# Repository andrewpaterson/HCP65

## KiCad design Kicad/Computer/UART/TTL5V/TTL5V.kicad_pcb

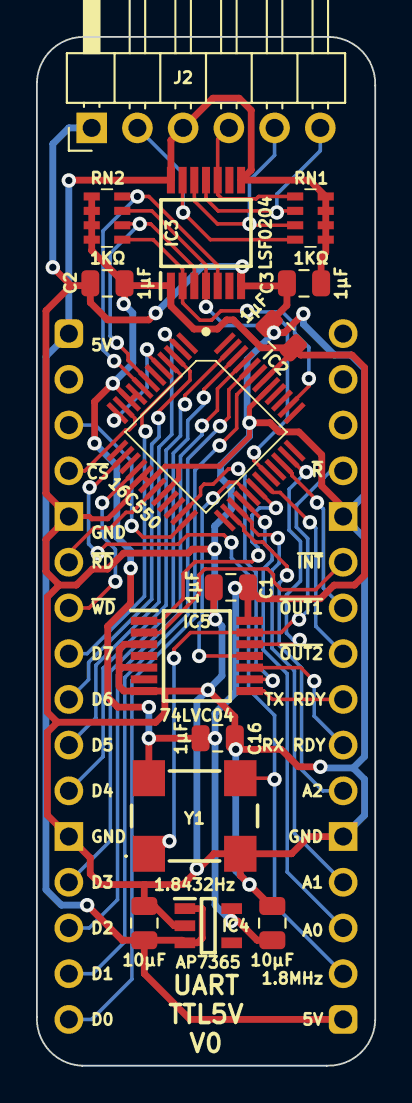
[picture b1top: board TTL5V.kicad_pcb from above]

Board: 2 copper layers, 18.8 x 57.2 mm, 16 parts (0 on the bottom side), 38 nets.

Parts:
C1, C2, C3, C15, C16: 1μF; C_0805
C17, C18: 10µF; C_0805
IC2: TL16C550DPTR; QFP50P900X900X160-48N
IC3: LSF0204PW-Q100J; SOP65P640X110-14N
IC4: AP7365-33WG-7; SOT95P285X130-5N
IC5: 74LVC04APW,118; SOP65P640X110-14N
J1: Board 2x16 W15.24mm; DIP-32_Board_W15.24mm_Nak
J2: Conn_01x06_Pin; PinHeader_1x06_P2.54mm_Horizontal
RN1, RN2: CAY16-102J4LF; CAY16-J4
Y1: LFSPXO020733

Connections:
1.8432MHz: IC2.14 (XIN), J1.18, Y1.3 (OUTPUT)
5V: C3.1, C17.1, IC3.8 (EN), IC3.14 (REFB), IC4.1 (6VIn), IC4.3 (EN), J1.1, J1.17, J2.3, RN1.5 (R4), RN1.6 (R3), RN1.7 (R2), RN1.8 (R1)
/3.3V: C1.1, C2.1, C15.1, C16.1, C18.1, IC2.9 (CS0), IC2.10 (CS1), IC2.42 (5V), IC3.1 (REFA), IC4.5 (3.3VOut), IC5.14 (3V), RN2.5 (R4), RN2.6 (R3), RN2.7 (R2), RN2.8 (R1), Y1.4 (3V)
/INT: IC2.30 (INTRPT), IC5.1 (1A)
/Reset: IC2.35 (MR), IC5.12 (6Y)
/SIN_{3V}: IC2.7 (SIN), IC3.3 (A1), RN2.2 (R2)
/SIN_{5V}: IC3.12 (B1), J2.5, RN1.3 (R3)
/SOUT_{3V}: IC2.8 (SOUT), IC3.5 (A3), RN2.4 (R4)
/SOUT_{5V}: IC3.10 (B3), J2.4, RN1.1 (R1)
/~CTS_{3V}: IC2.38 (~CTS), IC3.2 (A0), RN2.1 (R1)
/~CTS_{5V}: IC3.13 (B0), J2.2, RN1.4 (R4)
/~RTS_{3V}: IC2.32 (~RTS), IC3.4 (A2), RN2.3 (R3)
/~RTS_{5V}: IC3.11 (B2), J2.6, RN1.2 (R2)
/~RXRDY: IC2.29 (~RXRDY), IC5.11 (5A)
/~TXRDY: IC2.23 (~TXRDY), IC5.9 (4A)
A0: IC2.28 (A0), J1.19
A1: IC2.27 (A1), J1.20
A2: IC2.26 (A2), J1.22
D0: IC2.43 (D0), J1.16
D1: IC2.44 (D1), J1.15
D2: IC2.45 (D2), J1.14
D3: IC2.46 (D3), J1.13
D4: IC2.47 (D4), J1.11
D5: IC2.2 (D5), J1.10
D6: IC2.3 (D6), J1.9
D7: IC2.4 (D7), J1.8
GND: C1.2, C2.2, C3.2, C15.2, C16.2, C17.2, C18.2, IC2.17 (WR2), IC2.18 (GND), IC2.20 (RD2), IC2.41 (~RI), IC3.7 (GND), IC4.2 (GND), IC5.3 (2A), IC5.5 (3A), IC5.7 (GND), J1.5, J1.12, J1.21, J1.28, J2.1, Y1.2 (GND)
unnamed: IC2.5 (RCLK), IC2.12 (~BAUDOUT)
RX Ready: IC5.10 (5Y), J1.23
TX Ready: IC5.8 (4Y), J1.24
~ADS: IC2.24 (~ADS), J1.3
~CS: IC2.11 (~CS2), J1.4
~INT: IC5.2 (1Y), J1.27
~OUT1: IC2.34 (~OUT1), J1.26
~OUT2: IC2.31 (~OUT2), J1.25
~RD: IC2.19 (~RD1), J1.6
~Reset: IC5.13 (6A), J1.29, Y1.1 (EN)
~WD: IC2.16 (~WR1), J1.7

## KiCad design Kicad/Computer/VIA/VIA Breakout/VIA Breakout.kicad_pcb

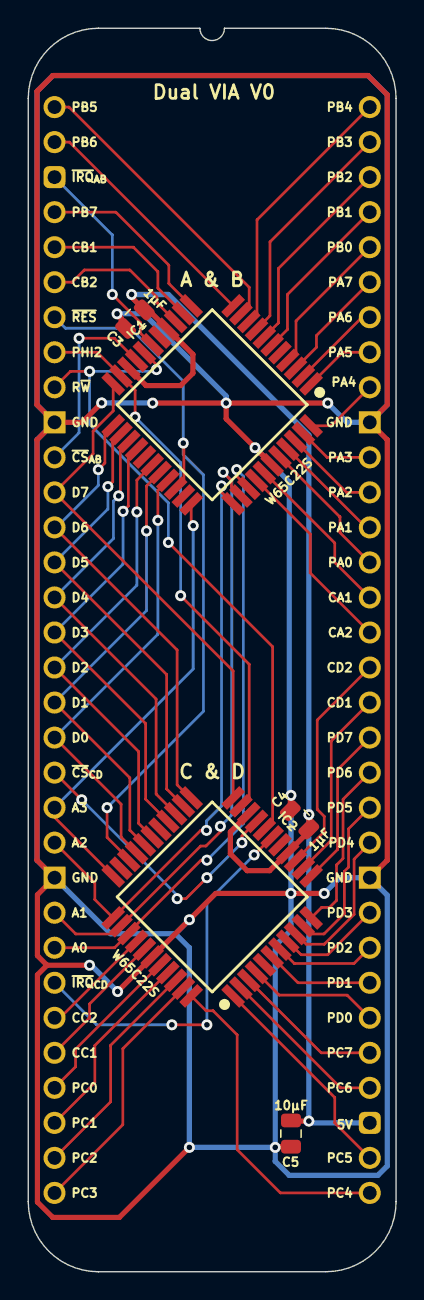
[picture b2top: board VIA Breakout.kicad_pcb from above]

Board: 2 copper layers, 26.7 x 90.2 mm, 6 parts (0 on the bottom side), 61 nets.

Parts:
C3, C4: 1μF; C_0805
C5: 10μF; C_0805
IC1, IC2: W65C22S6TQG-14; QFP80P1320X1320X270-44N
J1: Board 2x32 W22.86mm; DIP-64_Board_W22.86mm

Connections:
5V: C3.1, C4.1, C5.1, IC1.15 (5V), IC1.20 (CS1), IC2.15 (5V), IC2.20 (CS1), J1.35
A0: IC1.36 (RS0), IC2.36 (RS0), J1.25
A1: IC1.35 (RS1), IC2.35 (RS1), J1.24
A2: IC1.34 (RS2), IC2.34 (RS2), J1.22
A3: IC1.33 (RS3), IC2.33 (RS3), J1.21
CA1: IC1.38 (CA1), J1.50
CA2: IC1.37 (CA2), J1.49
CB1: IC1.13 (CB1), J1.5
CB2: IC1.14 (CB2), J1.6
CC1: IC2.38 (CA1), J1.28
CC2: IC2.37 (CA2), J1.27
CD1: IC2.13 (CB1), J1.47
CD2: IC2.14 (CB2), J1.48
D0: IC1.30 (D0), IC2.30 (D0), J1.19
D1: IC1.29 (D1), IC2.29 (D1), J1.18
D2: IC1.28 (D2), IC2.28 (D2), J1.17
D3: IC1.26 (D3), IC2.26 (D3), J1.16
D4: IC1.25 (D4), IC2.25 (D4), J1.15
D5: IC1.24 (D5), IC2.24 (D5), J1.14
D6: IC1.23 (D6), IC2.23 (D6), J1.13
D7: IC1.22 (D7), IC2.22 (D7), J1.12
Device ~CS_{AB}: IC1.19 (~CS2), J1.11
Device ~CS_{CD}: IC2.19 (~CS2), J1.20
GND: C3.2, C4.2, C5.2, IC1.39 (GND), IC2.39 (GND), J1.10, J1.23, J1.42, J1.55
PA0: IC1.40 (PA0), J1.51
PA1: IC1.41 (PA1), J1.52
PA2: IC1.42 (PA2), J1.53
PA3: IC1.43 (PA3), J1.54
PA4: IC1.44 (PA4), J1.56
PA5: IC1.1 (PA5), J1.57
PA6: IC1.2 (PA6), J1.58
PA7: IC1.3 (PA7), J1.59
PB0: IC1.4 (PB0), J1.60
PB1: IC1.6 (PB1), J1.61
PB2: IC1.7 (PB2), J1.62
PB3: IC1.8 (PB3), J1.63
PB4: IC1.9 (PB4), J1.64
PB5: IC1.10 (PB5), J1.1
PB6: IC1.11 (PB6), J1.2
PB7: IC1.12 (PB7), J1.4
PC0: IC2.40 (PA0), J1.29
PC1: IC2.41 (PA1), J1.30
PC2: IC2.42 (PA2), J1.31
PC3: IC2.43 (PA3), J1.32
PC4: IC2.44 (PA4), J1.33
PC5: IC2.1 (PA5), J1.34
PC6: IC2.2 (PA6), J1.36
PC7: IC2.3 (PA7), J1.37
PD0: IC2.4 (PB0), J1.38
PD1: IC2.6 (PB1), J1.39
PD2: IC2.7 (PB2), J1.40
PD3: IC2.8 (PB3), J1.41
PD4: IC2.9 (PB4), J1.43
PD5: IC2.10 (PB5), J1.44
PD6: IC2.11 (PB6), J1.45
PD7: IC2.12 (PB7), J1.46
PHI2: IC1.21 (PHI2), IC2.21 (PHI2), J1.8
R~W: IC1.18 (R~W), IC2.18 (R~W), J1.9
~IRQ_{AB}: IC1.17 (~IRQ), J1.3
~IRQ_{CD}: IC2.17 (~IRQ), J1.26
~Reset: IC1.31 (~RES), IC2.31 (~RES), J1.7

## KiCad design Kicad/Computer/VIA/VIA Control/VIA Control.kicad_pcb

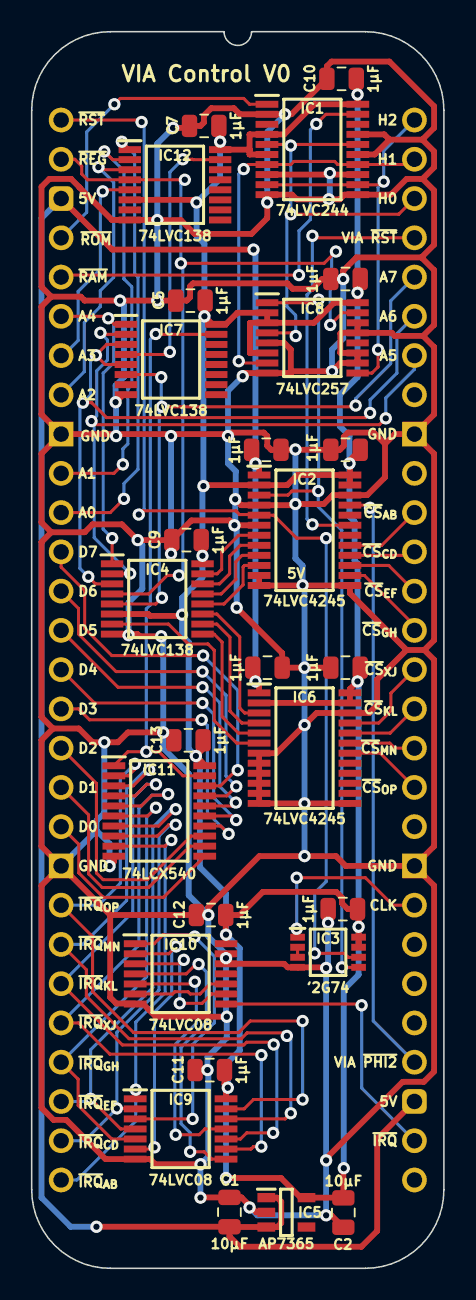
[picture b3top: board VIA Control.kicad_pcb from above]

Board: 2 copper layers, 26.7 x 80.0 mm, 28 parts (0 on the bottom side), 64 nets.

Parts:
C1, C2: 10μF; C_0805
C3, C4, C5, C6, C7, C8, C9, C10, C11, C12, C13, C14, C15: 1μF; C_0805
IC1: 74LVC244APW,118; SOP65P640X110-20N
IC2, IC6: 74LVC4245APW,118; SOP65P640X110-24N
IC3: 74LVC2G74DP,125; SOP65P400X110-8N
IC4, IC7, IC12: 74LVC138APW-Q100J; SOP65P640X110-16N
IC5: AP7365-33WG-7; SOT95P285X130-5N
IC8: 74LVC257APW,118; SOP65P640X110-16N
IC9, IC10: 74LVC08APW,112; SOP65P640X110-14N
IC11: 74LCX540FT; SOP65P640X120-20N
J3: Board 2x28 W22.86mm; DIP-56_Board_W22.86mm

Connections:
5V: C1.1, C4.1, C8.1, IC2.1 (5V), IC5.1 (6VIn), IC5.3 (EN), IC6.1 (5V), J3.3, J3.31
/1~Q: IC3.2 (D), IC3.3 (~Q)
/3.3V: C2.1, C3.1, C5.1, C6.1, C7.1, C9.1, C10.1, C11.1, C12.1, C13.1, C14.1, C15.1, IC1.4 (1A1), IC1.6 (1A2), IC1.20 (3V), IC2.2 (DIR), IC2.23 (3V), IC2.24 (3V), IC3.7 (~SD), IC3.8 (3V), IC4.6 (E3), IC4.16 (3V), IC5.5 (3.3VOut), IC6.2 (DIR), IC6.23 (3V), IC6.24 (3V), IC7.16 (3V), IC8.2 (1I0), IC8.3 (1I1), IC8.6 (2I1), IC8.16 (3V), IC9.14 (3V), IC10.14 (3V), IC11.20 (3V), IC12.6 (E3), IC12.16 (3V)
/CLK÷2: IC2.3 (A0), IC3.5 (Q), IC8.1 (S)
/~A0..A3: IC7.4 (~E1), IC12.15 (~Y0)
/~A0..A7: IC7.15 (~Y0), IC11.1 (~OE1), IC11.19 (~OE2)
/~AB•~CD: IC9.3 (1Y), IC10.1 (1A)
/~AB•~CD•~EF•~GH: IC10.3 (1Y), IC10.9 (3A)
/~CS_{AB}: IC2.7 (A4), IC4.15 (~Y0)
/~CS_{CD}: IC2.8 (A5), IC4.14 (~Y1)
/~CS_{EF}: IC2.9 (A6), IC4.13 (~Y2)
/~CS_{GH}: IC2.10 (A7), IC4.12 (~Y3)
/~CS_{KL}: IC4.10 (~Y5), IC6.4 (A1)
/~CS_{MN}: IC4.9 (~Y6), IC6.5 (A2)
/~CS_{OP}: IC4.7 (~Y7), IC6.6 (A3)
/~CS_{XJ}: IC4.11 (~Y4), IC6.3 (A0)
/~EF•~GH: IC9.6 (2Y), IC10.2 (1B)
/~MN•~OP: IC9.11 (4Y), IC10.5 (2B)
/~XJ•~KL: IC9.8 (3Y), IC10.4 (2A)
/~XJ•~KL•~MN•~OP: IC10.6 (2Y), IC10.10 (3B)
A0: IC12.1 (A0), J3.11
A1: IC12.2 (A1), J3.10
A2: IC12.3 (A2), J3.8
A3: IC12.5 (~E2), J3.7
A4: IC4.1 (A0), IC7.1 (A0), J3.6
A5: IC4.2 (A1), IC7.2 (A1), J3.50
A6: IC4.3 (A2), IC7.3 (A2), IC7.5 (~E2), J3.51
A7: IC4.5 (~E2), IC7.6 (E3), J3.52
CLK: IC3.1 (CP), J3.36
D0: IC11.11 (~Y8), J3.19
D1: IC11.12 (~Y7), J3.18
D2: IC11.13 (~Y6), J3.17
D3: IC11.14 (~Y5), J3.16
D4: IC11.15 (~Y4), J3.15
D5: IC11.16 (~Y3), J3.14
D6: IC11.17 (~Y2), J3.13
D7: IC11.18 (~Y1), J3.12
GND: C1.2, C2.2, C3.2, C4.2, C5.2, C6.2, C7.2, C8.2, C9.2, C10.2, C11.2, C12.2, C13.2, C14.2, C15.2, IC1.2 (1A0), IC1.8 (1A3), IC1.10 (GND), IC1.11 (2A3), IC1.13 (2A2), IC1.15 (2A1), IC1.17 (2A0), IC2.4 (A1), IC2.6 (A3), IC2.11 (GND), IC2.12 (GND), IC2.13 (GND), IC2.22 (~OE), IC3.4 (GND), IC4.8 (GND), IC5.2 (GND), IC6.7 (A4), IC6.8 (A5), IC6.9 (A6), IC6.10 (A7), IC6.11 (GND), IC6.12 (GND), IC6.13 (GND), IC6.22 (~OE), IC7.8 (GND), IC8.5 (2I0), IC8.8 (GND), IC8.10 (3I1), IC8.11 (3I0), IC8.13 (4I1), IC8.14 (4I0), IC9.7 (GND), IC10.7 (GND), IC10.12 (4A), IC10.13 (4B), IC11.10 (GND), IC12.8 (GND), J3.9, J3.20, J3.37, J3.48
H0: IC1.5 (2Y1), IC1.16 (1Y1), IC8.4 (1Y), J3.54
H1: IC1.7 (2Y2), IC1.14 (1Y2), IC8.7 (2Y), J3.55
H2: IC1.9 (2Y3), IC1.12 (1Y3), IC8.9 (3Y), J3.56
VIA PHI2_{5V}: IC2.21 (B0), J3.32
~CS_{AB 5V}: IC2.17 (B4), J3.46
~CS_{CD 5V}: IC2.16 (B5), J3.45
~CS_{EF 5V}: IC2.15 (B6), J3.44
~CS_{GH 5V}: IC2.14 (B7), J3.43
~CS_{KL 5V}: IC6.20 (B1), J3.41
~CS_{MN 5V}: IC6.19 (B2), J3.40
~CS_{OP 5V}: IC6.18 (B3), J3.39
~CS_{XJ 5V}: IC6.21 (B0), J3.42
~Device RAM: IC1.19 (~2OE), J3.5
~Device ROM: IC1.1 (~1OE), J3.4
~Device Registers: IC4.4 (~E1), IC8.15 (~OE), IC12.4 (~E1), J3.2
~IRQ: IC10.8 (3Y), J3.30
~IRQ_{AB}: IC9.1 (1A), IC11.9 (A8), J3.28
~IRQ_{CD}: IC9.2 (1B), IC11.8 (A7), J3.27
~IRQ_{EF}: IC9.4 (2A), IC11.7 (A6), J3.26
~IRQ_{GH}: IC9.5 (2B), IC11.6 (A5), J3.25
~IRQ_{KL}: IC9.10 (3B), IC11.4 (A3), J3.23
~IRQ_{MN}: IC9.12 (4A), IC11.3 (A2), J3.22
~IRQ_{OP}: IC9.13 (4B), IC11.2 (A1), J3.21
~IRQ_{XJ}: IC9.9 (3A), IC11.5 (A4), J3.24
~Reset: IC2.5 (A2), IC3.6 (~RD), J3.1
~Reset_{5V}: IC2.19 (B2), J3.53

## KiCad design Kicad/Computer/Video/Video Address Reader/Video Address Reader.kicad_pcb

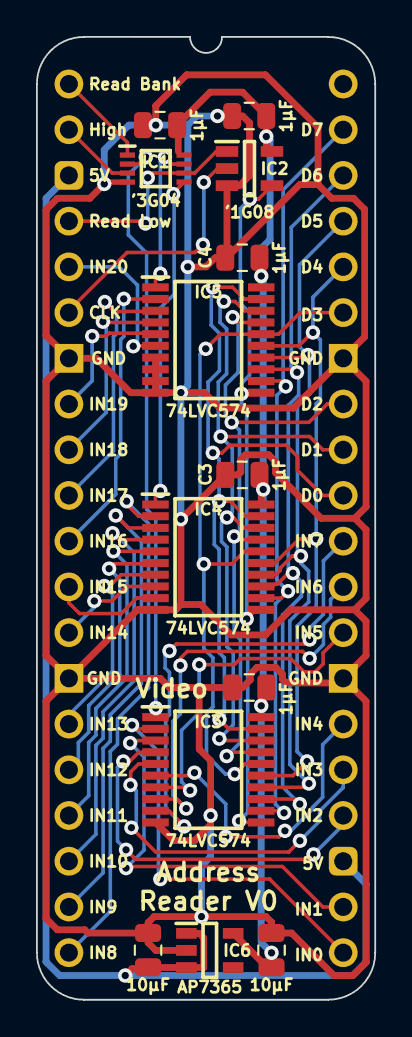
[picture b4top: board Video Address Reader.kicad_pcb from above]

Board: 2 copper layers, 18.8 x 53.5 mm, 14 parts (0 on the bottom side), 40 nets.

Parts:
C1, C2, C3, C4, C5: 1μF; C_0805
C6, C7: 10µF; C_0805
IC1: SN74LVC3G04DCUR; SOP50P310X90-8N
IC2: 74LVC1G08GV,125; SOT95P275X110-5N
IC3, IC4, IC5: 74LVC574APW,118; SOP65P640X110-20N
IC6: AP7365-33WG-7; SOT95P285X130-5N
J1: Board 2x20 W15.24mm; DIP-40_Board_W15.24mm

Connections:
5V: C6.1, IC6.1 (6VIn), IC6.3 (EN), J1.3, J1.23
/3.3V: C1.1, C2.1, C3.1, C4.1, C5.1, C7.1, IC1.8 (3V), IC2.5 (3V), IC3.20 (3V), IC4.20 (3V), IC5.20 (3V), IC6.5 (3.3VOut)
/PCLK·RAL: IC2.4 (Y), IC3.11 (CP), IC4.11 (CP), IC5.11 (CP)
/~Read Address Bank: IC1.7 (1Y), IC5.1 (~OE)
/~Read Address High: IC1.5 (2Y), IC4.1 (~OE)
/~Read Address Low: IC1.2 (3Y), IC3.1 (~OE)
C0: IC3.2 (D0), J1.21
C1: IC3.3 (D1), J1.22
C2: IC3.4 (D2), J1.24
C3: IC3.5 (D3), J1.25
C4: IC3.6 (D4), J1.26
C5: IC3.7 (D5), J1.28
C6: IC3.8 (D6), J1.29
C7: IC3.9 (D7), J1.30
C8: IC4.2 (D0), J1.20
C9: IC4.3 (D1), J1.19
C10: IC4.4 (D2), J1.18
C11: IC4.5 (D3), J1.17
C12: IC4.6 (D4), J1.16
C13: IC4.7 (D5), J1.15
C14: IC4.8 (D6), J1.13
C15: IC4.9 (D7), J1.12
C16: IC5.2 (D0), J1.11
C17: IC5.3 (D1), J1.10
C18: IC5.4 (D2), J1.9
C19: IC5.5 (D3), J1.8
C20: IC5.6 (D4), J1.5
D0: IC3.19 (Q0), IC4.19 (Q0), IC5.19 (Q0), J1.31
D1: IC3.18 (Q1), IC4.18 (Q1), IC5.18 (Q1), J1.32
D2: IC3.17 (Q2), IC4.17 (Q2), IC5.17 (Q2), J1.33
D3: IC3.16 (Q3), IC4.16 (Q3), IC5.16 (Q3), J1.35
D4: IC3.15 (Q4), IC4.15 (Q4), IC5.15 (Q4), J1.36
D5: IC3.14 (Q5), IC4.14 (Q5), IC5.14 (Q5), J1.37
D6: IC3.13 (Q6), IC4.13 (Q6), IC5.13 (Q6), J1.38
D7: IC3.12 (Q7), IC4.12 (Q7), IC5.12 (Q7), J1.39
GND: C1.2, C2.2, C3.2, C4.2, C5.2, C6.2, C7.2, IC1.4 (GND), IC2.3 (GND), IC3.10 (GND), IC4.10 (GND), IC5.7 (D5), IC5.8 (D6), IC5.9 (D7), IC5.10 (GND), IC6.2 (GND), J1.7, J1.14, J1.27, J1.34
Pixel CLK: IC2.2 (A), J1.6
Read Address Bank: IC1.1 (1A), J1.1
Read Address High: IC1.3 (2A), J1.2
Read Address Low: IC1.6 (3A), IC2.1 (B), J1.4

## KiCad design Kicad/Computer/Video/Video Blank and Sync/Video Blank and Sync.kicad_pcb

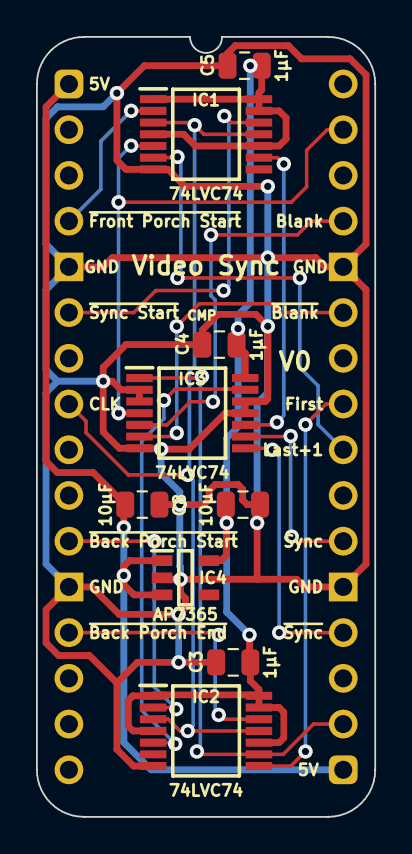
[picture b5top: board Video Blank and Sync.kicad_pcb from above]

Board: 2 copper layers, 18.8 x 43.3 mm, 10 parts (0 on the bottom side), 18 nets.

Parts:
C3, C4, C5: 1μF; C_0805
C8, C10: 10µF; C_0805
IC1, IC2, IC3: 74LVC74APW,118; SOP65P640X110-14N
IC4: AP7365-33WG-7; SOT95P285X130-5N
J1: Board 2x16 W15.24mm; DIP-32_Board_W15.24mm

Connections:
5V: C8.1, IC4.1 (6VIn), IC4.3 (EN), J1.1, J1.17
/3.3V: C3.1, C4.1, C5.1, C10.1, IC1.1 (~1RD), IC1.4 (~1SD), IC1.10 (~2SD), IC1.13 (~2RD), IC1.14 (3V), IC2.1 (~1RD), IC2.4 (~1SD), IC2.10 (~2SD), IC2.13 (~2RD), IC2.14 (3V), IC3.14 (3V), IC4.5 (3.3VOut)
/~Back Porch Start: IC2.5 (1Q), IC3.13 (~2RD)
/~Sync Start: IC1.9 (2Q), IC3.10 (~2SD)
Blank: IC3.5 (1Q), J1.29
CLK: IC1.3 (1CP), IC1.11 (2CP), IC2.3 (1CP), IC2.11 (2CP), J1.8
First: IC2.8 (~2Q), J1.25
GND: C3.2, C4.2, C5.2, C8.2, C10.2, IC1.7 (GND), IC2.7 (GND), IC3.2 (1D), IC3.3 (1CP), IC3.7 (GND), IC3.11 (2CP), IC3.12 (2D), IC4.2 (GND), J1.5, J1.12, J1.21, J1.28
Last + 1: IC1.6 (~1Q), J1.24
Sync: IC3.9 (2Q), J1.22
~Back Porch End: IC2.9 (2Q), IC3.1 (~1RD), J1.18
~Back Porch End _{CMP}: IC2.12 (2D), J1.13
~Back Porch Start _{CMP}: IC2.2 (1D), J1.11
~Blank: IC3.6 (~1Q), J1.27
~Front Porch Start: IC1.5 (1Q), IC3.4 (~1SD), J1.31
~Front Porch Start _{CMP}: IC1.2 (1D), J1.4
~Sync Start _{CMP}: IC1.12 (2D), J1.6
~Sync: IC3.8 (~2Q), J1.20

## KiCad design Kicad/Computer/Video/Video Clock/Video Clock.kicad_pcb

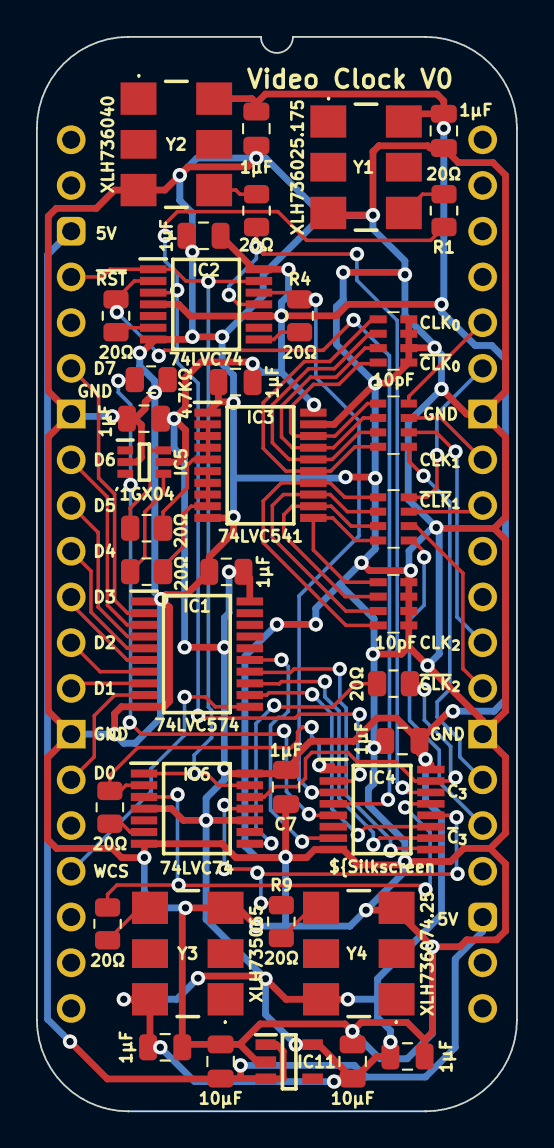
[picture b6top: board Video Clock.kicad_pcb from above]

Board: 2 copper layers, 26.7 x 59.7 mm, 39 parts (0 on the bottom side), 54 nets.

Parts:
C1, C2, C3, C4, C5, C6, C7, C8, C11, C12: 1μF; C_0805
C9, C10: 10μF; C_0805
CN1, CN2: CA0612KRX7R9BB100
IC1: 74LVC574APW,118; SOP65P640X110-20N
IC2, IC6: 74LVC74APW,118; SOP65P640X110-14N
IC3: 74LVC541APW,118; SOP65P640X110-20N
IC4: PI3B3251QE; SOP64P599X175-16N
IC5: 74LVC1GX04GW,125; SOP65P210X110-6N
IC11: AP7365-33WG-7; SOT95P285X130-5N
J4: Board 2x20 W22.86mm; DIP-40_Board_W22.86mm
R1, R2, R3, R4, R5, R6, R7, R8, R9, R10: 20Ω; R_0805
R11: 4.7KΩ; R_0805
RN1, RN2: CAY16-200J4LF; CAY16-F4
Y1: XLH736025.175000I; XLH736074250000I
Y2: XLH735040.000000I; XLH736074250000I
Y3: XLH735065.000000X; XLH735065000000X
Y4: XLH736074.250000I; XLH736074250000I

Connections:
5V: C9.1, IC11.1 (6VIn), IC11.3 (EN), J4.3, J4.23
/3.3V: C1.1, C2.1, C3.1, C4.1, C5.1, C6.1, C7.1, C8.1, C10.1, C11.1, C12.1, IC1.20 (3V), IC2.4 (~1SD), IC2.10 (~2SD), IC2.14 (3V), IC3.20 (3V), IC4.16 (3V), IC5.5 (3V), IC6.4 (~1SD), IC6.10 (~2SD), IC6.14 (3V), IC11.5 (3.3VOut), Y1.6 (3V), Y2.6 (3V), Y3.6 (3V), Y4.6 (3V)
/12.588MHz: IC2.2 (1D), IC4.4 (I0), R2.2
/20MHZ: IC2.12 (2D), IC4.3 (I1), R4.2
/25.175MHz: IC2.3 (1CP), IC4.2 (I2), R1.2
/32.5MHz: IC4.1 (I3), IC6.2 (1D), R8.2
/37.125MHz: IC4.15 (I4), IC6.12 (2D), R10.2
/40MHZ: IC2.11 (2CP), IC4.14 (I5), R3.2
/65MHZ: IC4.13 (I6), IC6.3 (1CP), R7.2
/74.25MHz: IC4.12 (I7), IC6.11 (2CP), R9.2
/Pixel CLK: IC3.2 (A0), IC3.3 (A1), IC3.4 (A2), IC3.5 (A3), R5.2
/Pixel CLK _{IN}: IC4.5 (Y), IC5.3 (X1), R11.1
/S0: IC1.12 (Q7), IC4.11 (S0)
/S1: IC1.13 (Q6), IC4.10 (S1)
/S2: IC1.14 (Q5), IC4.9 (S2)
/~OE: IC1.15 (Q4), IC4.7 (~OE)
/~Pixel CLK: IC3.6 (A4), IC3.7 (A5), IC3.8 (A6), IC3.9 (A7), R6.2
D0: IC1.9 (D7), J4.15
D1: IC1.8 (D6), J4.13
D2: IC1.7 (D5), J4.12
D3: IC1.6 (D4), J4.11
D4: IC1.5 (D3), J4.10
D5: IC1.4 (D2), J4.9
D6: IC1.3 (D1), J4.8
D7: IC1.2 (D0), J4.6
GND: C1.2, C2.2, C3.2, C4.2, C5.2, C6.2, C7.2, C8.2, C9.2, C10.2, C11.2, C12.2, CN1.5, CN1.6, CN1.7, CN1.8, CN2.5, CN2.6, CN2.7, CN2.8, IC1.1 (~OE), IC1.10 (GND), IC2.7 (GND), IC3.1 (~OE1), IC3.10 (GND), IC3.19 (~OE2), IC4.8 (GND), IC5.2 (GND), IC6.7 (GND), IC11.2 (GND), J4.7, J4.14, J4.27, J4.34, R11.2, Y1.3 (GND), Y2.3 (GND), Y3.3 (GND), Y4.3 (GND)
unnamed: IC2.6 (~1Q), R2.1
unnamed: IC2.8 (~2Q), R4.1
unnamed: CN2.4, IC3.18 (Y0), RN2.1 (R1)
unnamed: CN2.3, IC3.17 (Y1), RN2.2 (R2)
unnamed: CN2.2, IC3.16 (Y2), RN2.3 (R3)
unnamed: CN2.1, IC3.15 (Y3), RN2.4 (R4)
unnamed: CN1.4, IC3.14 (Y4), RN1.1 (R1)
unnamed: CN1.3, IC3.13 (Y5), RN1.2 (R2)
unnamed: CN1.2, IC3.12 (Y6), RN1.3 (R3)
unnamed: CN1.1, IC3.11 (Y7), RN1.4 (R4)
unnamed: IC5.6 (Y), R5.1
unnamed: IC5.4 (~Y), R6.1
unnamed: IC6.6 (~1Q), R8.1
unnamed: IC6.8 (~2Q), R10.1
unnamed: R1.1, Y1.4 (OUT)
unnamed: R3.1, Y2.4 (OUT)
unnamed: R7.1, Y3.4 (OUT)
unnamed: R9.1, Y4.4 (OUT)
Pixel CLK_{0}: J4.36, RN2.8 (R1)
Pixel CLK_{1}: J4.33, RN2.7 (R2)
Pixel CLK_{2}: J4.29, RN2.6 (R3)
Pixel CLK_{3}: J4.26, RN2.5 (R4)
Write Clock Select: IC1.11 (CP), J4.17
~Pixel CLK_{0}: J4.35, RN1.8 (R1)
~Pixel CLK_{1}: J4.32, RN1.7 (R2)
~Pixel CLK_{2}: J4.28, RN1.6 (R3)
~Pixel CLK_{3}: J4.25, RN1.5 (R4)
~Reset: IC2.1 (~1RD), IC2.13 (~2RD), IC6.1 (~1RD), IC6.13 (~2RD), J4.4

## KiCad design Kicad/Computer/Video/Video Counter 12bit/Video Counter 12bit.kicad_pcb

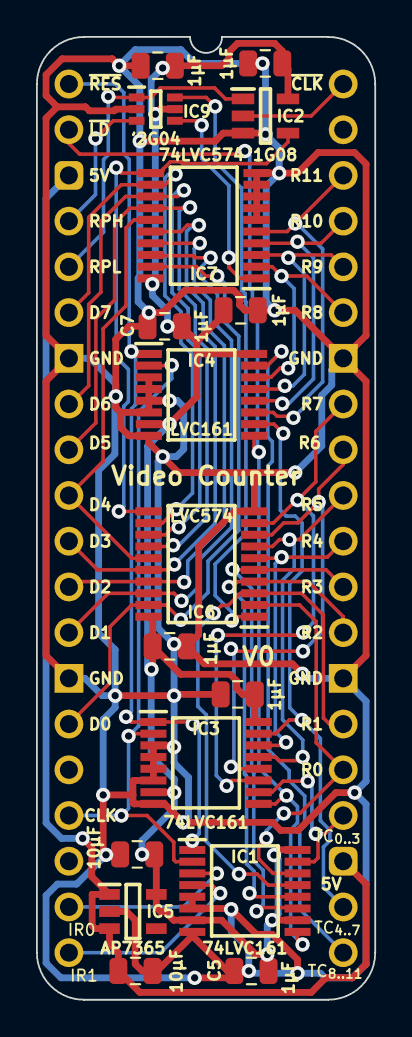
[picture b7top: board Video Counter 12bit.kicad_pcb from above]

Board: 2 copper layers, 18.8 x 53.5 mm, 18 parts (0 on the bottom side), 37 nets.

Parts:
C5, C6, C7, C10, C11, C12, C13: 1μF; C_0805
C8, C9: 10µF; C_0805
IC1, IC3, IC4: 74LVC161PW,112; SOP65P640X110-16N
IC2: 74LVC1G08GV,125; SOT95P275X110-5N
IC5: AP7365-33WG-7; SOT95P285X130-5N
IC6, IC7: 74LVC574APW,118; SOP65P640X110-20N
IC9: 74LVC2G04GW-Q100H; SOP65P210X110-6N
J3: Board 2x20 W15.24mm; DIP-40_Board_W15.24mm

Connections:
5V: C8.1, IC5.1 (6VIn), IC5.3 (EN), J3.3, J3.23
/3.3V: C5.1, C6.1, C7.1, C9.1, C10.1, C11.1, C12.1, C13.1, IC1.7 (CEP), IC1.10 (CET), IC1.16 (3V), IC2.5 (3V), IC3.7 (CEP), IC3.16 (3V), IC4.7 (CEP), IC4.16 (3V), IC5.5 (3.3VOut), IC6.20 (3V), IC7.20 (3V), IC9.5 (3V)
/Clock Read Row Position: IC2.4 (Y), IC6.11 (CP), IC7.11 (CP)
/~Read Row Position High: IC7.1 (~OE), IC9.4 (2Y)
/~Read Row Position Low: IC6.1 (~OE), IC9.6 (1Y)
CLK: IC1.2 (CP), IC3.2 (CP), IC4.2 (CP), J3.17
D0: IC6.19 (Q0), IC7.19 (Q0), J3.15
D1: IC6.18 (Q1), IC7.18 (Q1), J3.13
D2: IC6.17 (Q2), IC7.17 (Q2), J3.12
D3: IC6.16 (Q3), IC7.16 (Q3), J3.11
D4: IC6.15 (Q4), IC7.15 (Q4), J3.10
D5: IC6.14 (Q5), IC7.14 (Q5), J3.9
D6: IC6.13 (Q6), IC7.13 (Q6), J3.8
D7: IC6.12 (Q7), IC7.12 (Q7), J3.6
GND: C5.2, C6.2, C7.2, C8.2, C9.2, C10.2, C11.2, C12.2, C13.2, IC1.5 (D2), IC1.6 (D3), IC1.8 (GND), IC2.3 (GND), IC3.3 (D0), IC3.4 (D1), IC3.5 (D2), IC3.6 (D3), IC3.8 (GND), IC4.3 (D0), IC4.4 (D1), IC4.5 (D2), IC4.6 (D3), IC4.8 (GND), IC5.2 (GND), IC6.10 (GND), IC7.6 (D4), IC7.7 (D5), IC7.8 (D6), IC7.9 (D7), IC7.10 (GND), IC9.2 (GND), J3.7, J3.14, J3.27, J3.34
IR0: IC1.3 (D0), J3.19
IR1: IC1.4 (D1), J3.20
R0: IC1.14 (Q0), IC6.2 (D0), J3.25
R1: IC1.13 (Q1), IC6.3 (D1), J3.26
R2: IC1.12 (Q2), IC6.4 (D2), J3.28
R3: IC1.11 (Q3), IC6.5 (D3), J3.29
R4: IC3.14 (Q0), IC6.6 (D4), J3.30
R5: IC3.13 (Q1), IC6.7 (D5), J3.31
R6: IC3.12 (Q2), IC6.8 (D6), J3.32
R7: IC3.11 (Q3), IC6.9 (D7), J3.33
R8: IC4.14 (Q0), IC7.2 (D0), J3.35
R9: IC4.13 (Q1), IC7.3 (D1), J3.36
R10: IC4.12 (Q2), IC7.4 (D2), J3.37
R11: IC4.11 (Q3), IC7.5 (D3), J3.38
Read Row Position High: IC9.3 (2A), J3.4
Read Row Position Low: IC2.1 (B), IC9.1 (1A), J3.5
TC_{0..3}: IC1.15 (TC), IC3.10 (CET), J3.24
TC_{4..7}: IC3.15 (TC), IC4.10 (CET), J3.22
TC_{8..11}: IC4.15 (TC), J3.21
~CLK: IC2.2 (A), J3.40
~Load: IC1.9 (~PE), IC3.9 (~PE), IC4.9 (~PE), J3.2
~Reset: IC1.1 (~MR), IC3.1 (~MR), IC4.1 (~MR), J3.1

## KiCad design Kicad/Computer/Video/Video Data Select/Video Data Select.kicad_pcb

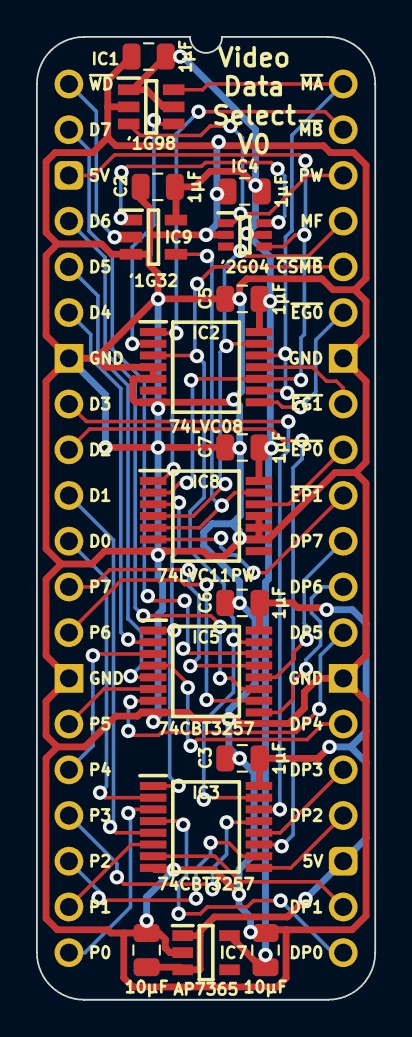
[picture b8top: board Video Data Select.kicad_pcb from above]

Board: 2 copper layers, 18.8 x 53.5 mm, 18 parts (0 on the bottom side), 41 nets.

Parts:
C1, C2, C3, C4, C5, C6, C7: 1μF; C_0805
C8, C9: 10μF; C_0805
IC1: SN74LVC1G98DBVR; SOT95P280X145-6N
IC2: 74LVC08APW,112; SOP65P640X110-14N
IC3, IC5: SN74CBT3257CPWR; SOP65P640X120-16N
IC4: 74LVC2G04GW-Q100H; SOP65P210X110-6N
IC7: AP7365-33WG-7; SOT95P285X130-5N
IC8: 74LVC11PW,112; SOP65P640X110-14N
IC9: 74LVC1G32GV,125; SOT95P275X110-5N
J1: Board 2x20 W15.24mm; DIP-40_Board_W15.24mm

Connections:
5V: C3.1, C6.1, C8.1, IC3.16 (5V), IC5.16 (5V), IC7.1 (6VIn), IC7.3 (EN), J1.23
/3.3V: C1.1, C2.1, C4.1, C5.1, C7.1, C9.1, IC1.1 (IN1), IC1.5 (3V), IC2.14 (3V), IC4.5 (3V), IC7.5 (3.3VOut), IC8.14 (3V), IC9.5 (3V)
/~Palette + WD: IC8.5 (2C), IC8.13 (1C), IC9.4 (Y)
/~Palette Write Memory B: IC1.4 (Y), IC2.2 (1B)
/~Palette Write: IC4.6 (1Y), IC9.1 (B)
DM0: IC3.2 (1B1), J1.11
DM1: IC3.5 (2B1), J1.10
DM2: IC3.11 (3B1), J1.9
DM3: IC3.14 (4B1), J1.8
DM4: IC5.2 (1B1), J1.6
DM5: IC5.5 (2B1), J1.5
DM6: IC5.11 (3B1), J1.4
DM7: IC5.14 (4B1), J1.2
DP0: IC3.4 (1A), J1.21
DP1: IC3.7 (2A), J1.22
DP2: IC3.9 (3A), J1.24
DP3: IC3.12 (4A), J1.25
DP4: IC5.4 (1A), J1.26
DP5: IC5.7 (2A), J1.28
DP6: IC5.9 (3A), J1.29
DP7: IC5.12 (4A), J1.30
GND: C1.2, C2.2, C3.2, C4.2, C5.2, C6.2, C7.2, C8.2, C9.2, IC1.2 (GND), IC2.4 (2A), IC2.5 (2B), IC2.7 (GND), IC3.8 (GND), IC4.2 (GND), IC5.8 (GND), IC7.2 (GND), IC8.7 (GND), IC8.9 (3A), IC8.10 (3B), IC8.11 (3C), IC9.3 (GND), J1.7, J1.14, J1.27, J1.34
Memory Frame: IC2.13 (4B), IC4.3 (2A), IC8.4 (2B), J1.37
PL0: IC3.3 (1B2), J1.20
PL1: IC3.6 (2B2), J1.19
PL2: IC3.10 (3B2), J1.18
PL3: IC3.13 (4B2), J1.17
PL4: IC5.3 (1B2), J1.16
PL5: IC5.6 (2B2), J1.15
PL6: IC5.10 (3B2), J1.13
PL7: IC5.13 (4B2), J1.12
Palette Write: IC1.3 (IN0), IC4.1 (1A), J1.38
~CS Memory B: IC2.3 (1Y), IC3.15 (~OE), IC5.15 (~OE), J1.36
~EG0: IC2.8 (3Y), J1.35
~EG1: IC2.11 (4Y), J1.33
~EP0: IC8.12 (1Y), J1.32
~EP1: IC8.6 (2Y), J1.31
~Main WD: IC9.2 (A), J1.1
~Memory A: IC1.6 (IN2), IC2.9 (3A), IC2.12 (4A), J1.40
~Memory B: IC2.1 (1A), IC3.1 (S), IC5.1 (S), IC8.1 (1A), IC8.3 (2A), J1.39
~Memory Frame: IC2.10 (3B), IC4.4 (2Y), IC8.2 (1B), J1.3
